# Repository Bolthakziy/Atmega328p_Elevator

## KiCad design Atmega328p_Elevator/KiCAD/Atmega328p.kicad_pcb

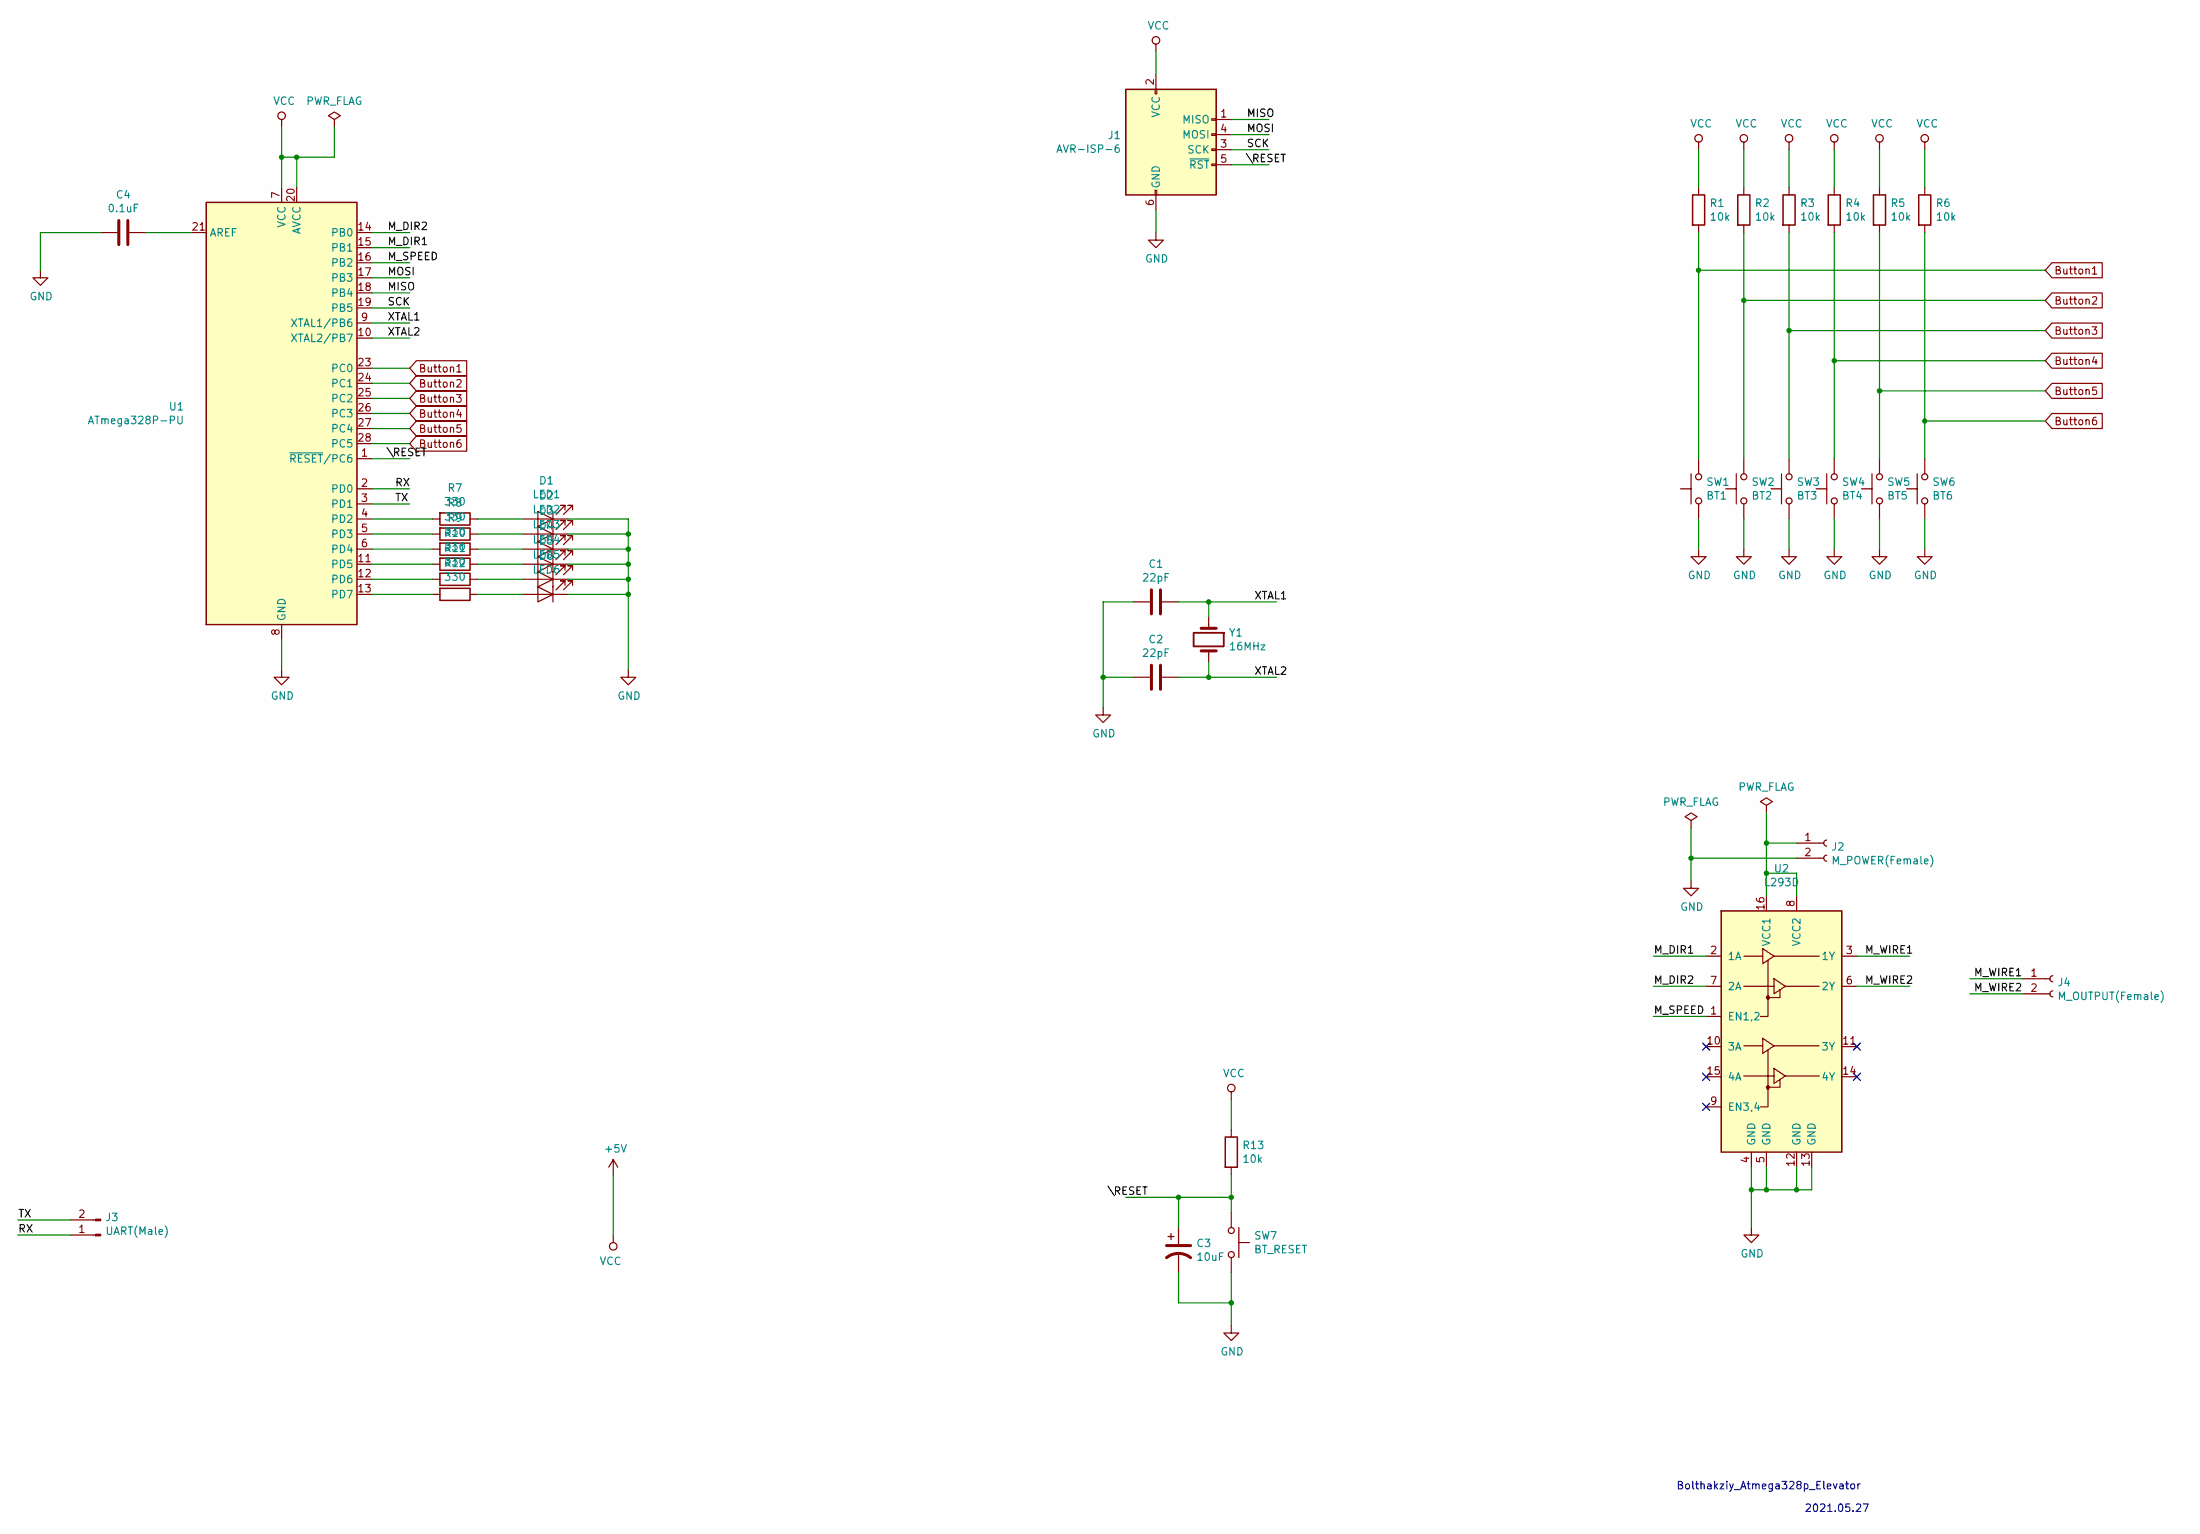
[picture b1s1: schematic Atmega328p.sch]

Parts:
C1, C2: 22pF; C_0402_1005Metric
C3: 10uF; CP_Radial_D4.0mm_P2.00mm
C4: 0.1uF; C_0402_1005Metric
D1: LED1; LED_D1.8mm_W3.3mm_H2.4mm
D2: LED2; LED_D1.8mm_W3.3mm_H2.4mm
D3: LED3; LED_D1.8mm_W3.3mm_H2.4mm
D4: LED4; LED_D1.8mm_W3.3mm_H2.4mm
D5: LED5; LED_D1.8mm_W3.3mm_H2.4mm
D6: LED6; LED_D1.8mm_W3.3mm_H2.4mm
J1: AVR-ISP-6; PinSocket_2x03_P2.54mm_Vertical
J2: M_POWER(Female); PinHeader_1x02_P2.00mm_Vertical
J3: UART(Male); PinSocket_1x02_P2.00mm_Vertical
J4: M_OUTPUT(Female); PinHeader_1x02_P2.00mm_Vertical
R1, R2, R3, R4, R5, R6, R13: 10k; R_Axial_DIN0204_L3.6mm_D1.6mm_P2.54mm_Vertical
R7, R8, R9, R10, R11, R12: 330; R_Axial_DIN0204_L3.6mm_D1.6mm_P2.54mm_Vertical
SW1: BT1; SW_PUSH_6mm
SW2: BT2; SW_PUSH_6mm
SW3: BT3; SW_PUSH_6mm
SW4: BT4; SW_PUSH_6mm
SW5: BT5; SW_PUSH_6mm
SW6: BT6; SW_PUSH_6mm
SW7: BT_RESET; SW_PUSH_6mm
U1: ATmega328P-PU; DIP-28_W7.62mm
U2: L293D; DIP-16_W7.62mm
Y1: 16MHz; Crystal_HC49-U_Vertical

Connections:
+5V: J1.2 (VCC), R1.1, R2.1, R3.1, R4.1, R5.1, R6.1, R13.1, U1.7 (VCC), U1.20 (AVCC)
/MISO: J1.1 (MISO), U1.18 (PB4)
/MOSI: J1.4 (MOSI), U1.17 (PB3)
/M_DIR1: U1.15 (PB1), U2.2 (1A)
/M_DIR2: U1.14 (PB0), U2.7 (2A)
/M_SPEED: U1.16 (PB2), U2.1 (EN1,2)
/M_WIRE1: J4.1, U2.3 (1Y)
/M_WIRE2: J4.2, U2.6 (2Y)
/RX: J3.1, U1.2 (PD0)
/SCK: J1.3 (SCK), U1.19 (PB5)
/TX: J3.2, U1.3 (PD1)
/XTAL1: C1.1, U1.9 (XTAL1/PB6), Y1.1
/XTAL2: C2.1, U1.10 (XTAL2/PB7), Y1.2
/\RESET: C3.1, J1.5 (~RST), R13.2, SW7.1, U1.1 (~RESET~/PC6)
Button1: R1.2, SW1.2, U1.23 (PC0)
Button2: R2.2, SW2.2, U1.24 (PC1)
Button3: R3.2, SW3.2, U1.25 (PC2)
Button4: R4.2, SW4.2, U1.26 (PC3)
Button5: R5.2, SW5.2, U1.27 (PC4)
Button6: R6.2, SW6.2, U1.28 (PC5)
GND: C1.2, C2.2, C3.2, C4.2, D1.1 (K), D2.1 (K), D3.1 (K), D4.1 (K), D5.1 (K), D6.1 (K), J1.6 (GND), J2.2, SW1.1, SW2.1, SW3.1, SW4.1, SW5.1, SW6.1, SW7.2, U1.8 (GND), U1.22 (GND), U2.4 (GND), U2.5 (GND), U2.12 (GND), U2.13 (GND)
unnamed: C4.1, U1.21 (AREF)
unnamed: D1.2 (A), R7.1
unnamed: D2.2 (A), R8.1
unnamed: D3.2 (A), R9.1
unnamed: D4.2 (A), R10.1
unnamed: D5.2 (A), R11.1
unnamed: D6.2 (A), R12.1
unnamed: J2.1, U2.8 (VCC2), U2.16 (VCC1)
unnamed: R7.2, U1.4 (PD2)
unnamed: R8.2, U1.5 (PD3)
unnamed: R9.2, U1.6 (PD4)
unnamed: R10.2, U1.11 (PD5)
unnamed: R11.2, U1.12 (PD6)
unnamed: R12.2, U1.13 (PD7)

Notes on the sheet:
Bolthakziy_Atmega328p_Elevator
2021.05.27

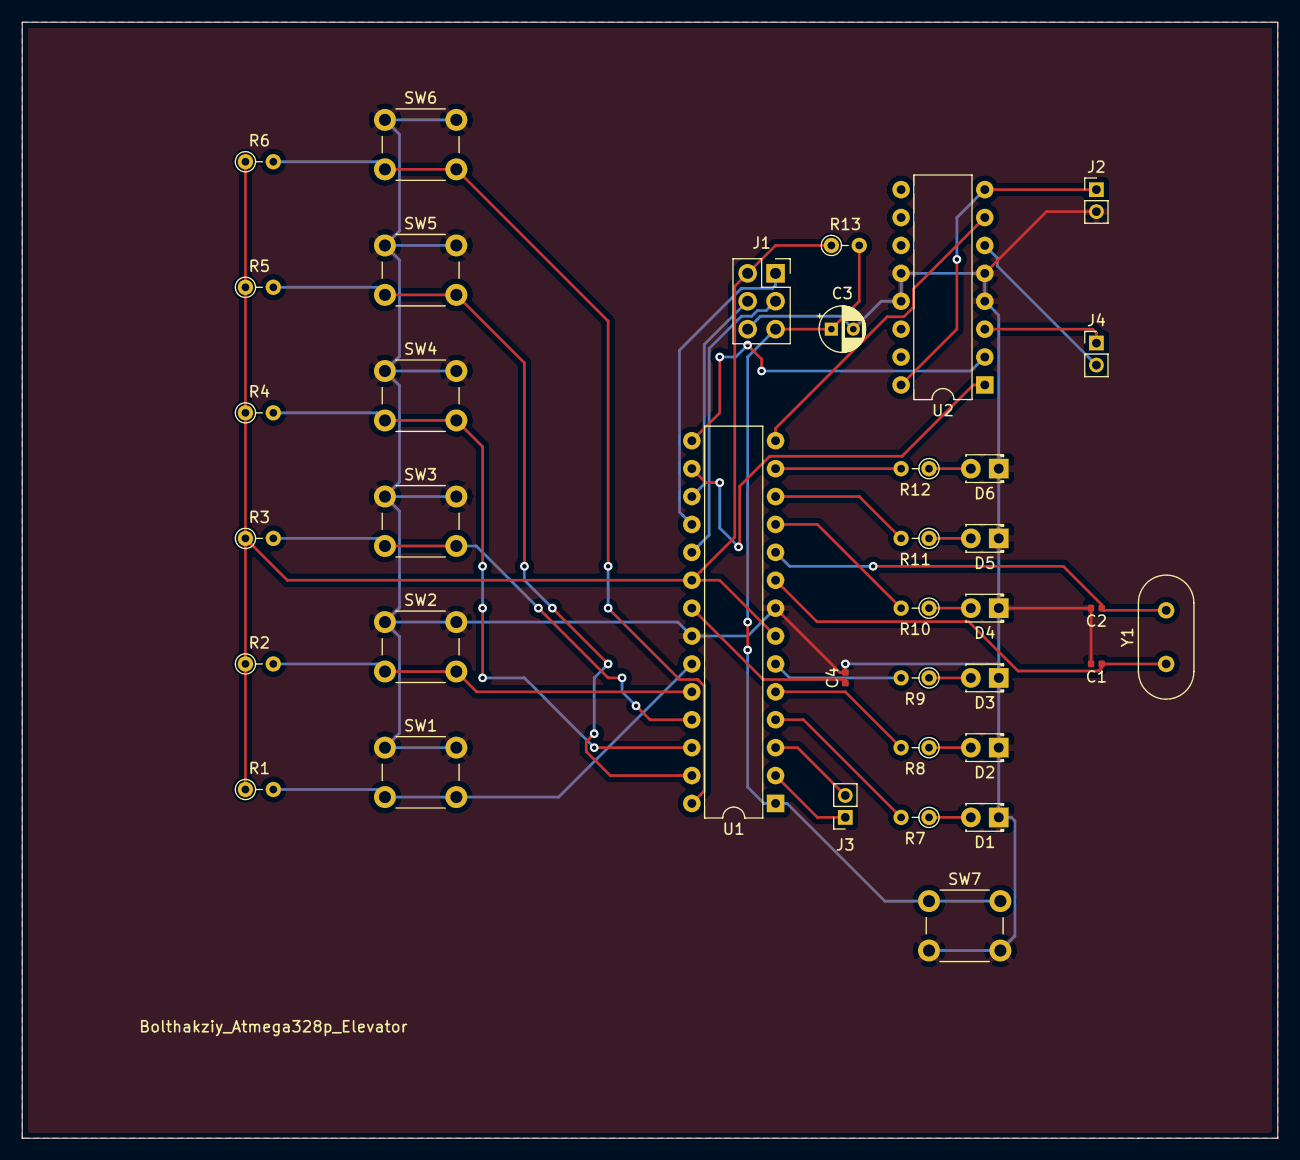
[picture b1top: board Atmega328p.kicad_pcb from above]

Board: 2 copper layers, 114.3 x 101.6 mm, 37 parts (0 on the bottom side), 35 nets.

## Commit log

2021-07-05 Create PCB
